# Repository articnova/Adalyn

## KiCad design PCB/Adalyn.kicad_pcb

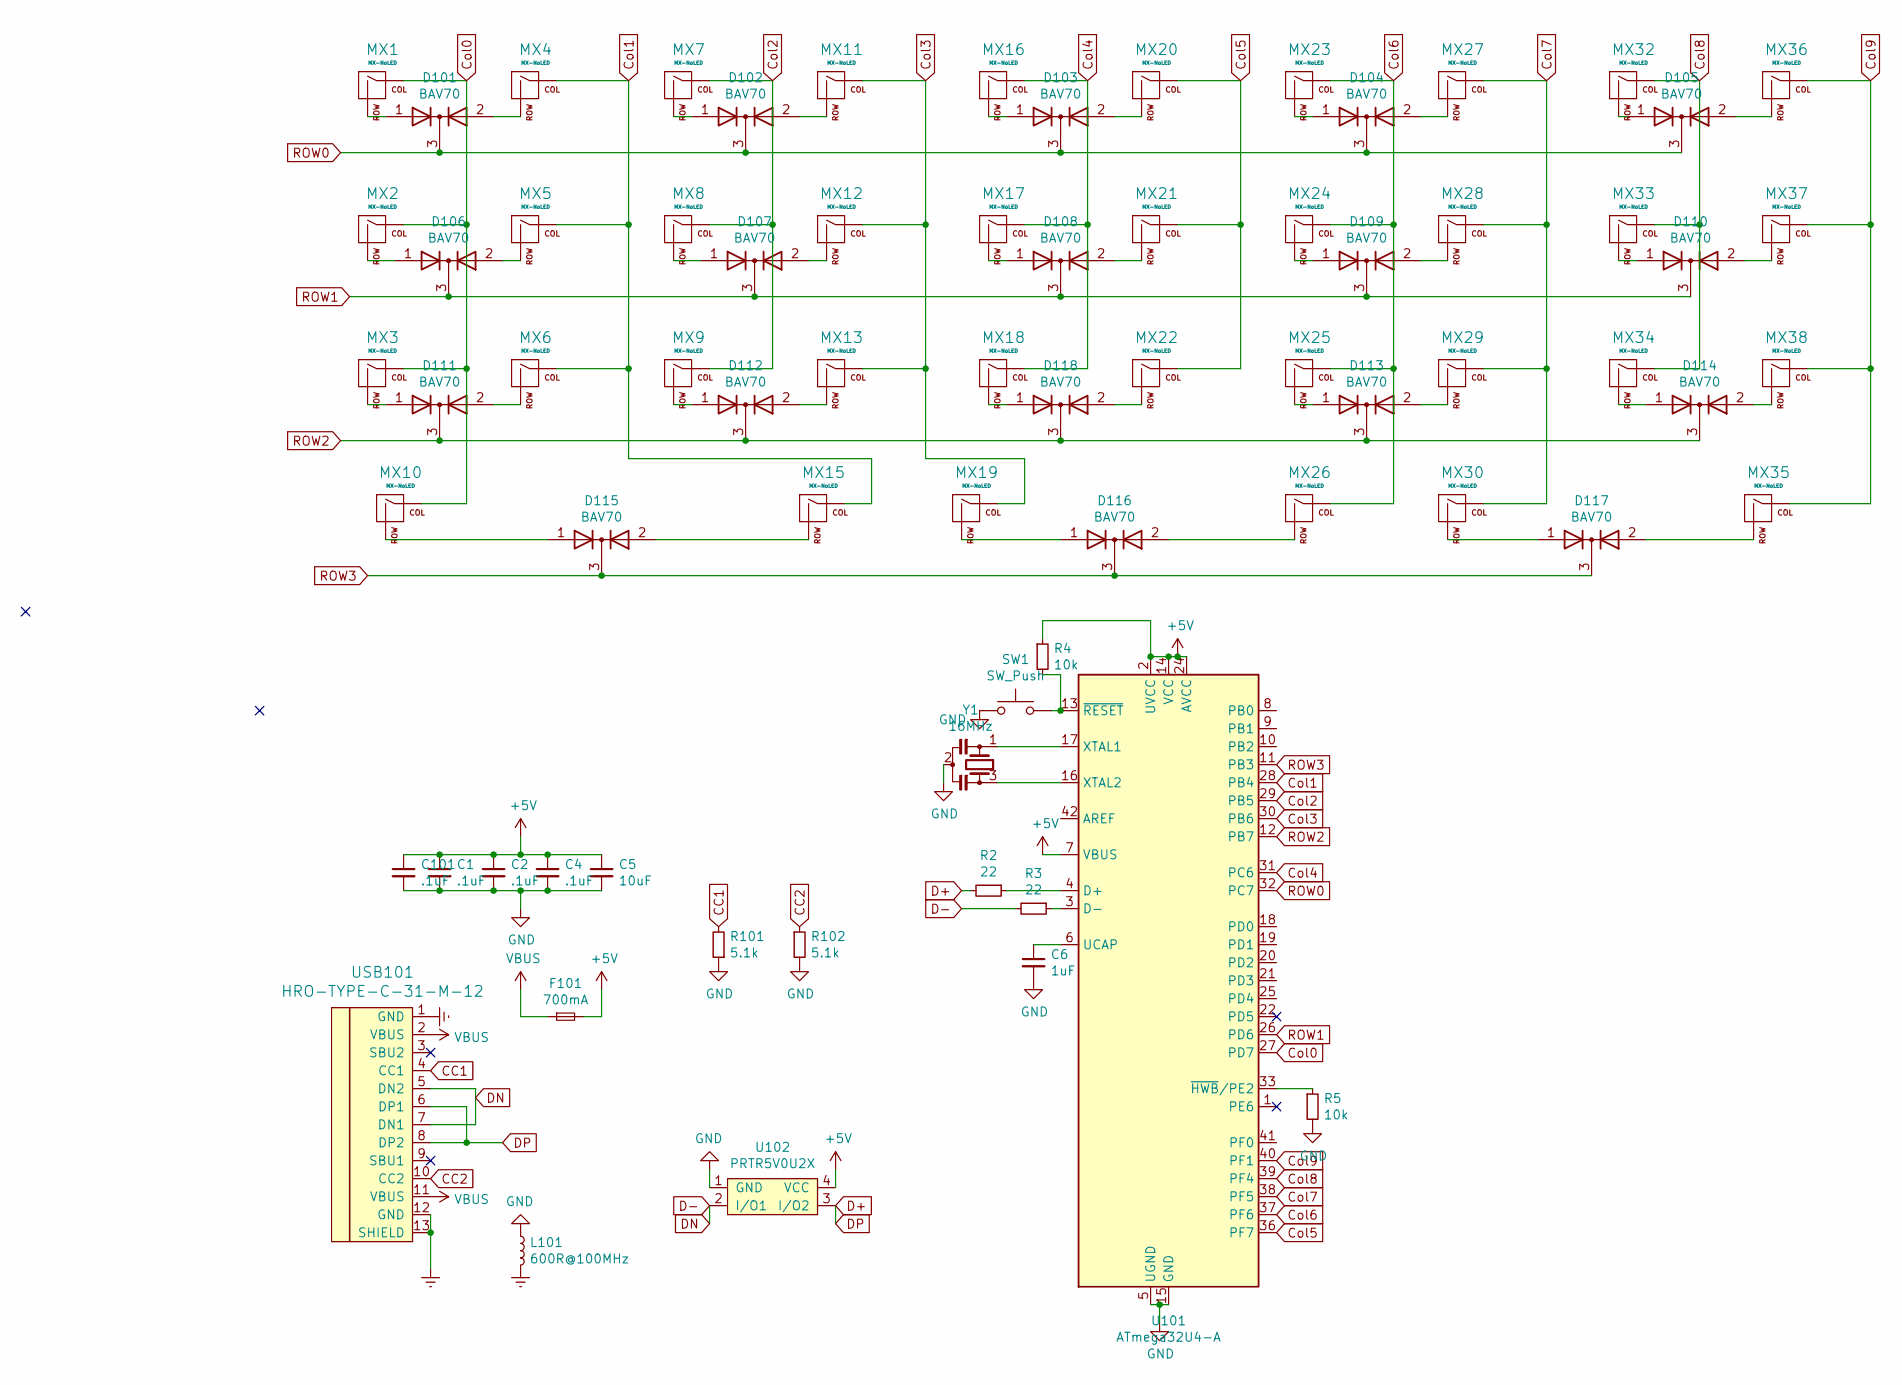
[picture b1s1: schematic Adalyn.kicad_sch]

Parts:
C1, C2, C4, C101: .1uF; C_0603_1608Metric_Pad1.08x0.95mm_HandSolder
C5: 10uF; C_0603_1608Metric_Pad1.08x0.95mm_HandSolder
C6: 1uF; C_0603_1608Metric_Pad1.08x0.95mm_HandSolder
D101, D102, D103, D104, D105, D106, D107, D108, D109, D110, D111, D112, D113, D114, D115, D116, D117, D118: BAV70; SOT-23
F101: 700mA; Fuse_0603_1608Metric
L101: 600R@100MHz; L_0603_1608Metric
MX1, MX2, MX3, MX4, MX5, MX6, MX7, MX8, MX9, MX10, MX11, MX12, MX13, MX15, MX16, MX17, MX18, MX19, MX20, MX21, MX22, MX23, MX24, MX25, MX26, MX27, MX28, MX29, MX30, MX32, MX33, MX34, MX35, MX36, MX37, MX38: MX-NoLED; MXOnly-1U-NoLED
R2, R3: 22; R_0603_1608Metric_Pad0.98x0.95mm_HandSolder
R4, R5: 10k; R_0603_1608Metric_Pad0.98x0.95mm_HandSolder
R101, R102: 5.1k; R_0603_1608Metric
SW1: SW_Push; SW_SPST_TL3342
U101: ATmega32U4-A; TQFP-44_10x10mm_P0.8mm
U102: PRTR5V0U2X; SOT-143
USB101: HRO-TYPE-C-31-M-12; HRO-TYPE-C-31-M-12-Assembly
Y1: 16MHz; Resonator_SMD_Murata_CSTxExxV-3Pin_3.0x1.1mm_HandSoldering

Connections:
+5V: C1.1, C2.1, C4.1, C5.1, C101.1, F101.2, R4.1, U101.2 (UVCC), U101.7 (VBUS), U101.14 (VCC), U101.24 (AVCC), U101.34 (VCC), U101.44 (AVCC), U102.4 (VCC)
CC1: R101.2, USB101.4 (CC1)
CC2: R102.1, USB101.10 (CC2)
Col0: MX1.1 (COL), MX2.1 (COL), MX3.1 (COL), MX10.1 (COL), U101.27 (PD7)
Col1: MX4.1 (COL), MX5.1 (COL), MX6.1 (COL), MX15.1 (COL), U101.28 (PB4)
Col2: MX7.1 (COL), MX8.1 (COL), MX9.1 (COL), U101.29 (PB5)
Col3: MX11.1 (COL), MX12.1 (COL), MX13.1 (COL), MX19.1 (COL), U101.30 (PB6)
Col4: MX16.1 (COL), MX17.1 (COL), MX18.1 (COL), U101.31 (PC6)
Col5: MX20.1 (COL), MX21.1 (COL), MX22.1 (COL), U101.36 (PF7)
Col6: MX23.1 (COL), MX24.1 (COL), MX25.1 (COL), MX26.1 (COL), U101.37 (PF6)
Col7: MX27.1 (COL), MX28.1 (COL), MX29.1 (COL), MX30.1 (COL), U101.38 (PF5)
Col8: MX32.1 (COL), MX33.1 (COL), MX34.1 (COL), U101.39 (PF4)
Col9: MX35.1 (COL), MX36.1 (COL), MX37.1 (COL), MX38.1 (COL), U101.40 (PF1)
D+: R2.2, U102.3 (I/O2), USB101.6 (DP1), USB101.8 (DP2)
D-: R3.2, U102.2 (I/O1), USB101.5 (DN2), USB101.7 (DN1)
Earth: L101.2, USB101.1 (GND), USB101.12 (GND), USB101.13 (SHIELD)
GND: C1.2, C2.2, C4.2, C5.2, C6.2, C101.2, L101.1, R5.2, R101.1, R102.2, SW1.1, U101.5 (UGND), U101.15 (GND), U101.23 (GND), U101.35 (GND), U101.43 (GND), U102.1 (GND), Y1.2
unnamed: C6.1, U101.6 (UCAP)
unnamed: D101.1 (A), MX1.2 (ROW)
unnamed: D101.2 (A), MX4.2 (ROW)
unnamed: D102.1 (A), MX7.2 (ROW)
unnamed: D102.2 (A), MX11.2 (ROW)
unnamed: D103.1 (A), MX16.2 (ROW)
unnamed: D103.2 (A), MX20.2 (ROW)
unnamed: D104.1 (A), MX23.2 (ROW)
unnamed: D104.2 (A), MX27.2 (ROW)
unnamed: D105.1 (A), MX32.2 (ROW)
unnamed: D105.2 (A), MX36.2 (ROW)
unnamed: D106.1 (A), MX2.2 (ROW)
unnamed: D106.2 (A), MX5.2 (ROW)
unnamed: D107.1 (A), MX8.2 (ROW)
unnamed: D107.2 (A), MX12.2 (ROW)
unnamed: D108.1 (A), MX17.2 (ROW)
unnamed: D108.2 (A), MX21.2 (ROW)
unnamed: D109.1 (A), MX24.2 (ROW)
unnamed: D109.2 (A), MX28.2 (ROW)
unnamed: D110.1 (A), MX33.2 (ROW)
unnamed: D110.2 (A), MX37.2 (ROW)
unnamed: D111.1 (A), MX3.2 (ROW)
unnamed: D111.2 (A), MX6.2 (ROW)
unnamed: D112.1 (A), MX9.2 (ROW)
unnamed: D112.2 (A), MX13.2 (ROW)
unnamed: D113.1 (A), MX25.2 (ROW)
unnamed: D113.2 (A), MX29.2 (ROW)
unnamed: D114.1 (A), MX34.2 (ROW)
unnamed: D114.2 (A), MX38.2 (ROW)
unnamed: D115.1 (A), MX10.2 (ROW)
unnamed: D115.2 (A), MX15.2 (ROW)
unnamed: D116.1 (A), MX19.2 (ROW)
unnamed: D116.2 (A), MX26.2 (ROW)
unnamed: D117.1 (A), MX30.2 (ROW)
unnamed: D117.2 (A), MX35.2 (ROW)
unnamed: D118.1 (A), MX18.2 (ROW)
unnamed: D118.2 (A), MX22.2 (ROW)
unnamed: R2.1, U101.4 (D+)
unnamed: R3.1, U101.3 (D-)
unnamed: R4.2, SW1.2, U101.13 (~RESET)
unnamed: R5.1, U101.33 (~HWB/PE2)
unnamed: U101.16 (XTAL2), Y1.3
unnamed: U101.17 (XTAL1), Y1.1
ROW0: D101.3 (K), D102.3 (K), D103.3 (K), D104.3 (K), D105.3 (K), U101.32 (PC7)
ROW1: D106.3 (K), D107.3 (K), D108.3 (K), D109.3 (K), D110.3 (K), U101.26 (PD6)
ROW2: D111.3 (K), D112.3 (K), D113.3 (K), D114.3 (K), D118.3 (K), U101.12 (PB7)
ROW3: D115.3 (K), D116.3 (K), D117.3 (K), U101.11 (PB3)
VBUS: F101.1, USB101.2 (VBUS), USB101.11 (VBUS)

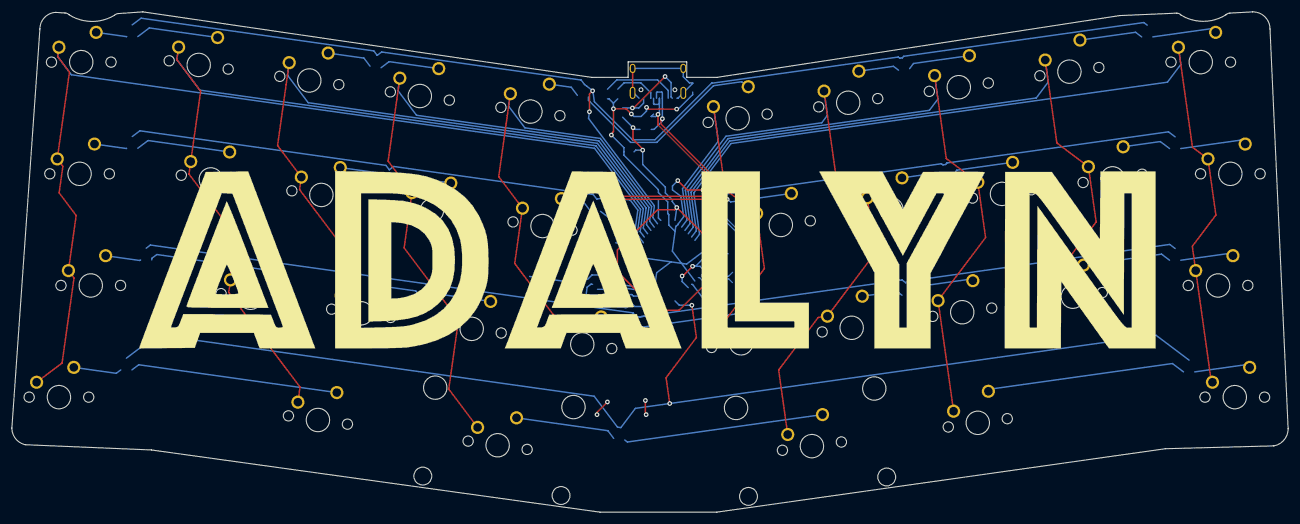
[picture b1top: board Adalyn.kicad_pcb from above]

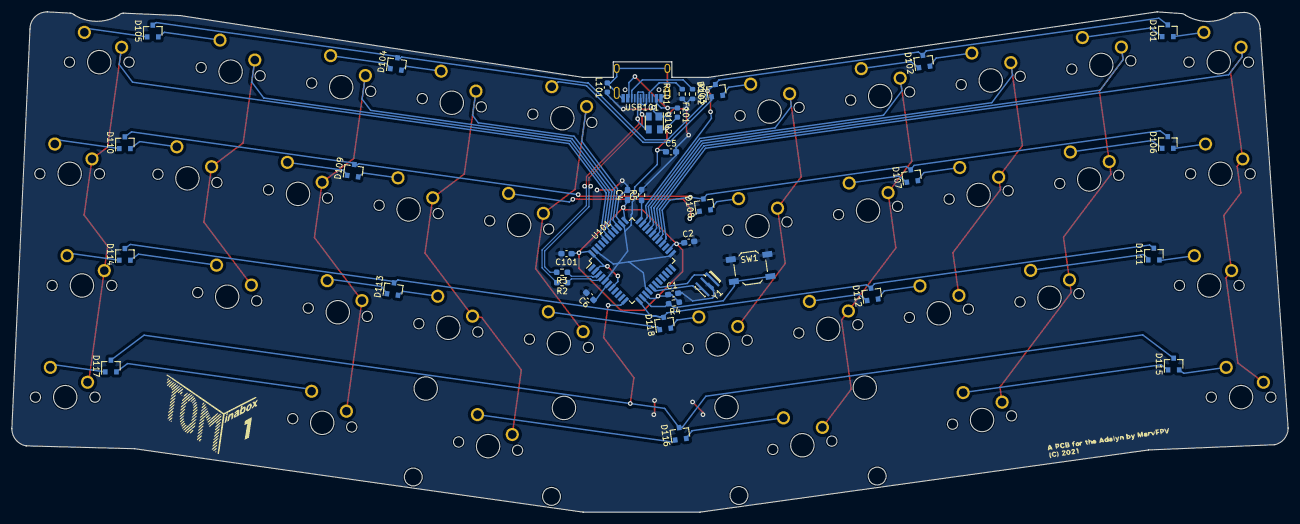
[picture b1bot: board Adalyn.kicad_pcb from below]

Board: 2 copper layers, 217.7 x 85.3 mm, 73 parts (37 on the bottom side), 65 nets.

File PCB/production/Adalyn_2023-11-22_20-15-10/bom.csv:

Designator,Footprint,Quantity,Value,LCSC Part #
"C1, C101, C2, C4",0603,4,.1uF,
C5,0603,1,10uF,
C6,0603,1,1uF,
"D101, D102, D103, D104, D105, D106, D107, D108, D109, D110, D111, D112, D113, D114, D115, D116, D117, D118",SOT-23,18,BAV70,
F101,0603,1,700mA,
L101,0603,1,600R@100MHz,
"MX1, MX10, MX11, MX12, MX13, MX15, MX16, MX17, MX18, MX2, MX20, MX21, MX22, MX23, MX24, MX25, MX27, MX28, MX29, MX3, MX30, MX32, MX33, MX34, MX35, MX36, MX37, MX38, MX4, MX5, MX6, MX7, MX8, MX9",MXOnly-1U-NoLED,34,MX-NoLED,
MX19,MXOnly-2.25U-ReversedStabilizers-NoLED,1,MX-NoLED,
MX26,MXOnly-2U-ReversedStabilizers-NoLED,1,MX-NoLED,
"R101, R102",0603,2,5.1k,
"R2, R3",0603,2,22,
"R4, R5",0603,2,10k,
SW1,SW_SPST_TL3342,1,SW_Push,
U101,TQFP-44_10x10mm_P0.8mm,1,ATmega32U4-A,
U102,SOT-143,1,PRTR5V0U2X,
USB101,HRO-TYPE-C-31-M-12-Assembly,1,HRO-TYPE-C-31-M-12,
Y1,Resonator_SMD_Murata_CSTxExxV-3Pin_3.0x1.1mm_HandSoldering,1,16MHz,

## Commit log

2023-11-22 BOM + CPL for JLCPCB
